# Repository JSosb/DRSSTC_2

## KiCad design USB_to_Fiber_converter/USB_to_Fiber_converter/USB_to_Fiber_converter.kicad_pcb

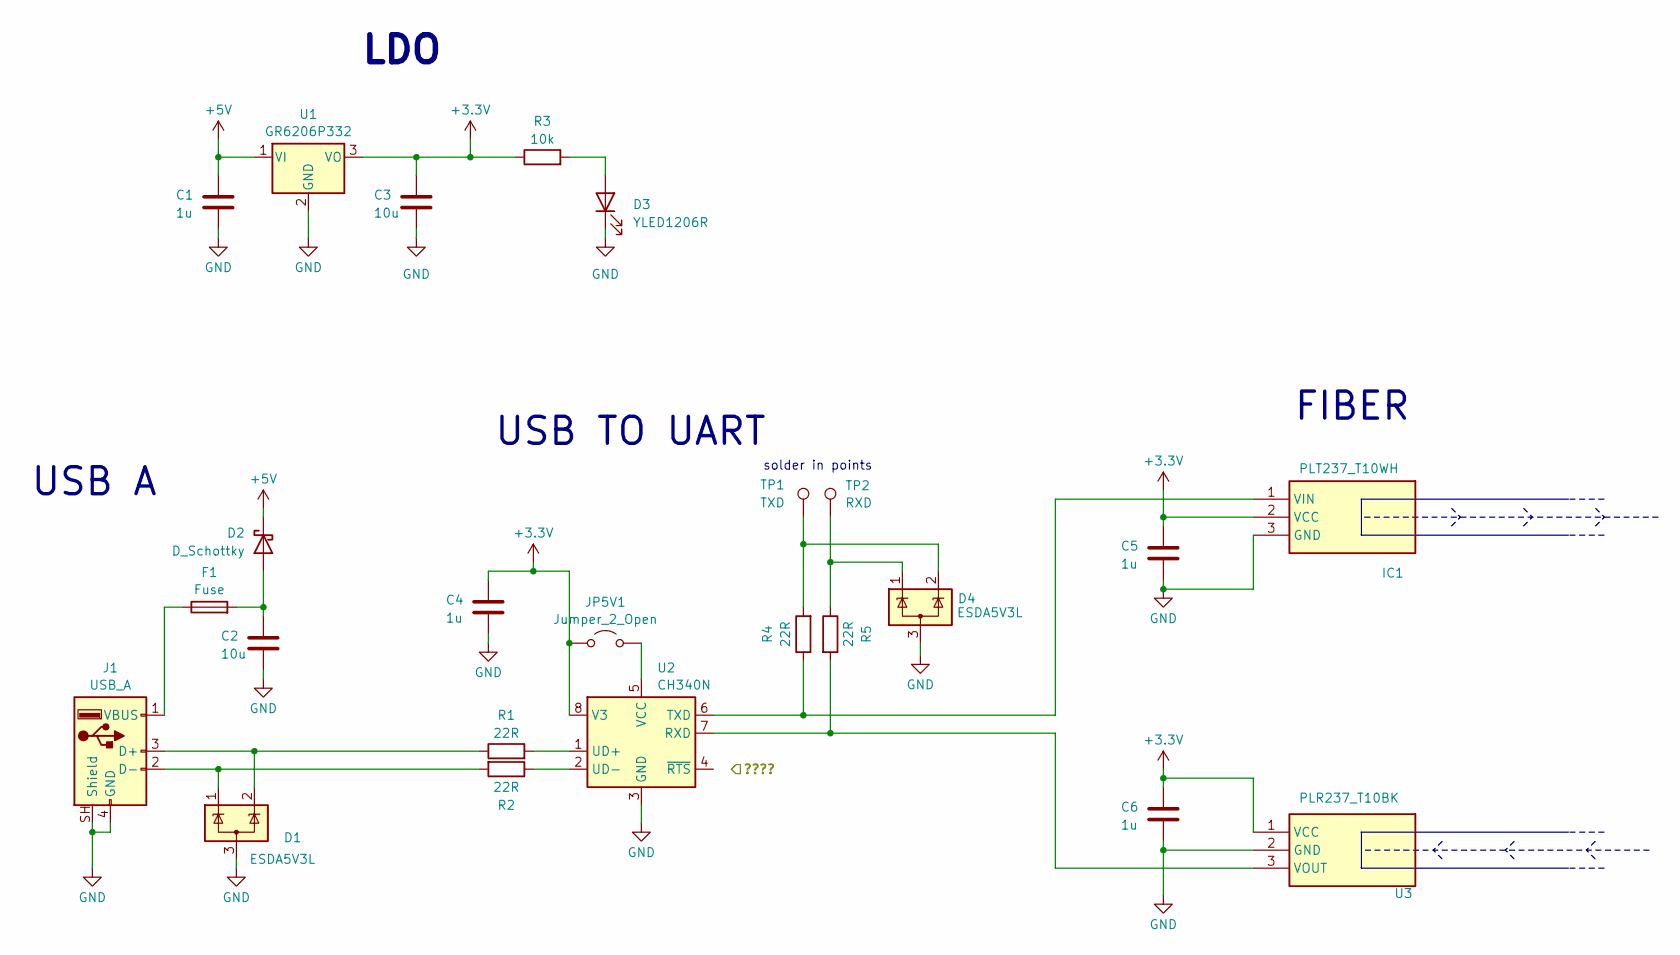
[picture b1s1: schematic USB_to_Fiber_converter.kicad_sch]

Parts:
C1, C4, C5, C6: 1u; C_0603_1608Metric
C2, C3: 10u; C_0805_2012Metric
D1, D4: ESDA5V3L; SOT-23-3
D2: D_Schottky; D_SOD-128
D3: YLED1206R; LED_1206_3216Metric
F1: Fuse; Fuse_2512_6332Metric
IC1: PLT237_T10WH; PLT237T10WH; Mouser Part Number 638-PLT237/T10WH
J1: USB_A; USB_A_Receptacle_GCT_USB1046
JP5V1: Jumper_2_Open; SolderJumper-2_P1.3mm_Open_Pad1.0x1.5mm
R1, R2, R4, R5: 22R; R_0603_1608Metric
R3: 10k; R_0805_2012Metric
TP1: TXD; TestPoint_Pad_2.0x2.0mm
TP2: RXD; TestPoint_Pad_2.0x2.0mm
U1: GR6206P332; SOT-23-3
U2: CH340N; JEITA_SOIC-8_3.9x4.9mm_P1.27mm
U3: PLR237_T10BK; PLR237T10BK; Mouser Part Number 638-PLR237/T10BK

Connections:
+3.3V: C3.1, C4.1, C5.1, C6.1, IC1.2 (VCC), JP5V1.1 (A), R3.1, U1.3 (VO), U2.8 (V3), U3.1 (VCC)
+5V: C1.1, D2.1 (K), U1.1 (VI)
GND: C1.2, C2.2, C3.2, C4.2, C5.2, C6.2, D1.3 (A), D3.1 (K), D4.3 (A), IC1.3 (GND), J1.4 (GND), J1.SH (Shield), U1.2 (GND), U2.3 (GND), U3.2 (GND)
unnamed: C2.1, D2.2 (A), F1.2
unnamed: D3.2 (A), R3.2
unnamed: D4.1 (K), R5.1, TP2.1 (1_1)
unnamed: D4.2 (K), R4.2, TP1.1 (1_1)
unnamed: IC1.1 (VIN), R4.1, U2.6 (TXD)
unnamed: D1.2 (K), J1.3 (D+), R1.1
unnamed: D1.1 (K), J1.2 (D-), R2.2
unnamed: F1.1, J1.1 (VBUS)
unnamed: JP5V1.2 (B), U2.5 (VCC)
unnamed: R5.2, U2.7 (RXD), U3.3 (VOUT)
unnamed: R1.2, U2.1 (UD+)
unnamed: R2.1, U2.2 (UD-)

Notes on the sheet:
FIBER
LDO
USB A
USB TO UART
solder in points

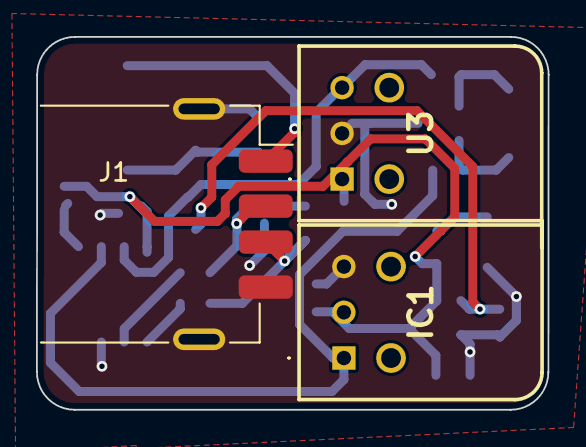
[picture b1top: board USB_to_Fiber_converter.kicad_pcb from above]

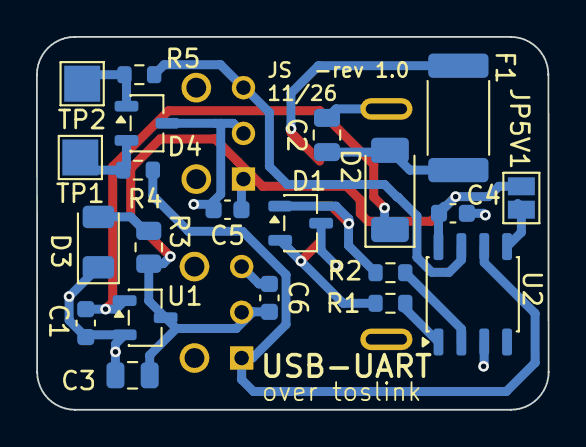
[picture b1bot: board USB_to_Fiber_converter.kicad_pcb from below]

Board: 2 copper layers, 28.4 x 20.7 mm, 24 parts (21 on the bottom side), 15 nets.

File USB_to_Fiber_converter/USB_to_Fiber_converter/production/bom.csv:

Designator,Footprint,Quantity,Value,LCSC Part #
"C1, C4, C5, C6",0603,4,1u,
"C2, C3",0805,2,10u,
"D1, D4",SOT-23-3,2,ESDA5V3L,
D2,D_SOD-128,1,D_Schottky,
D3,1206,1,YLED1206R,
F1,2512,1,Fuse,
IC1,PLT237T10WH,1,PLT237_T10WH,
J1,USB_A_Receptacle_GCT_USB1046,1,USB_A,
JP5V1,SolderJumper-2_P1.3mm_Open_Pad1.0x1.5mm,1,Jumper_2_Open,
"R1, R2, R4, R5",0603,4,22R,
R3,0805,1,10k,
TP1,TestPoint_Pad_2.0x2.0mm,1,TXD,
TP2,TestPoint_Pad_2.0x2.0mm,1,RXD,
U1,SOT-23-3,1,GR6206P332,
U2,JEITA_SOIC-8_3.9x4.9mm_P1.27mm,1,CH340N,
U3,PLR237T10BK,1,PLR237_T10BK,

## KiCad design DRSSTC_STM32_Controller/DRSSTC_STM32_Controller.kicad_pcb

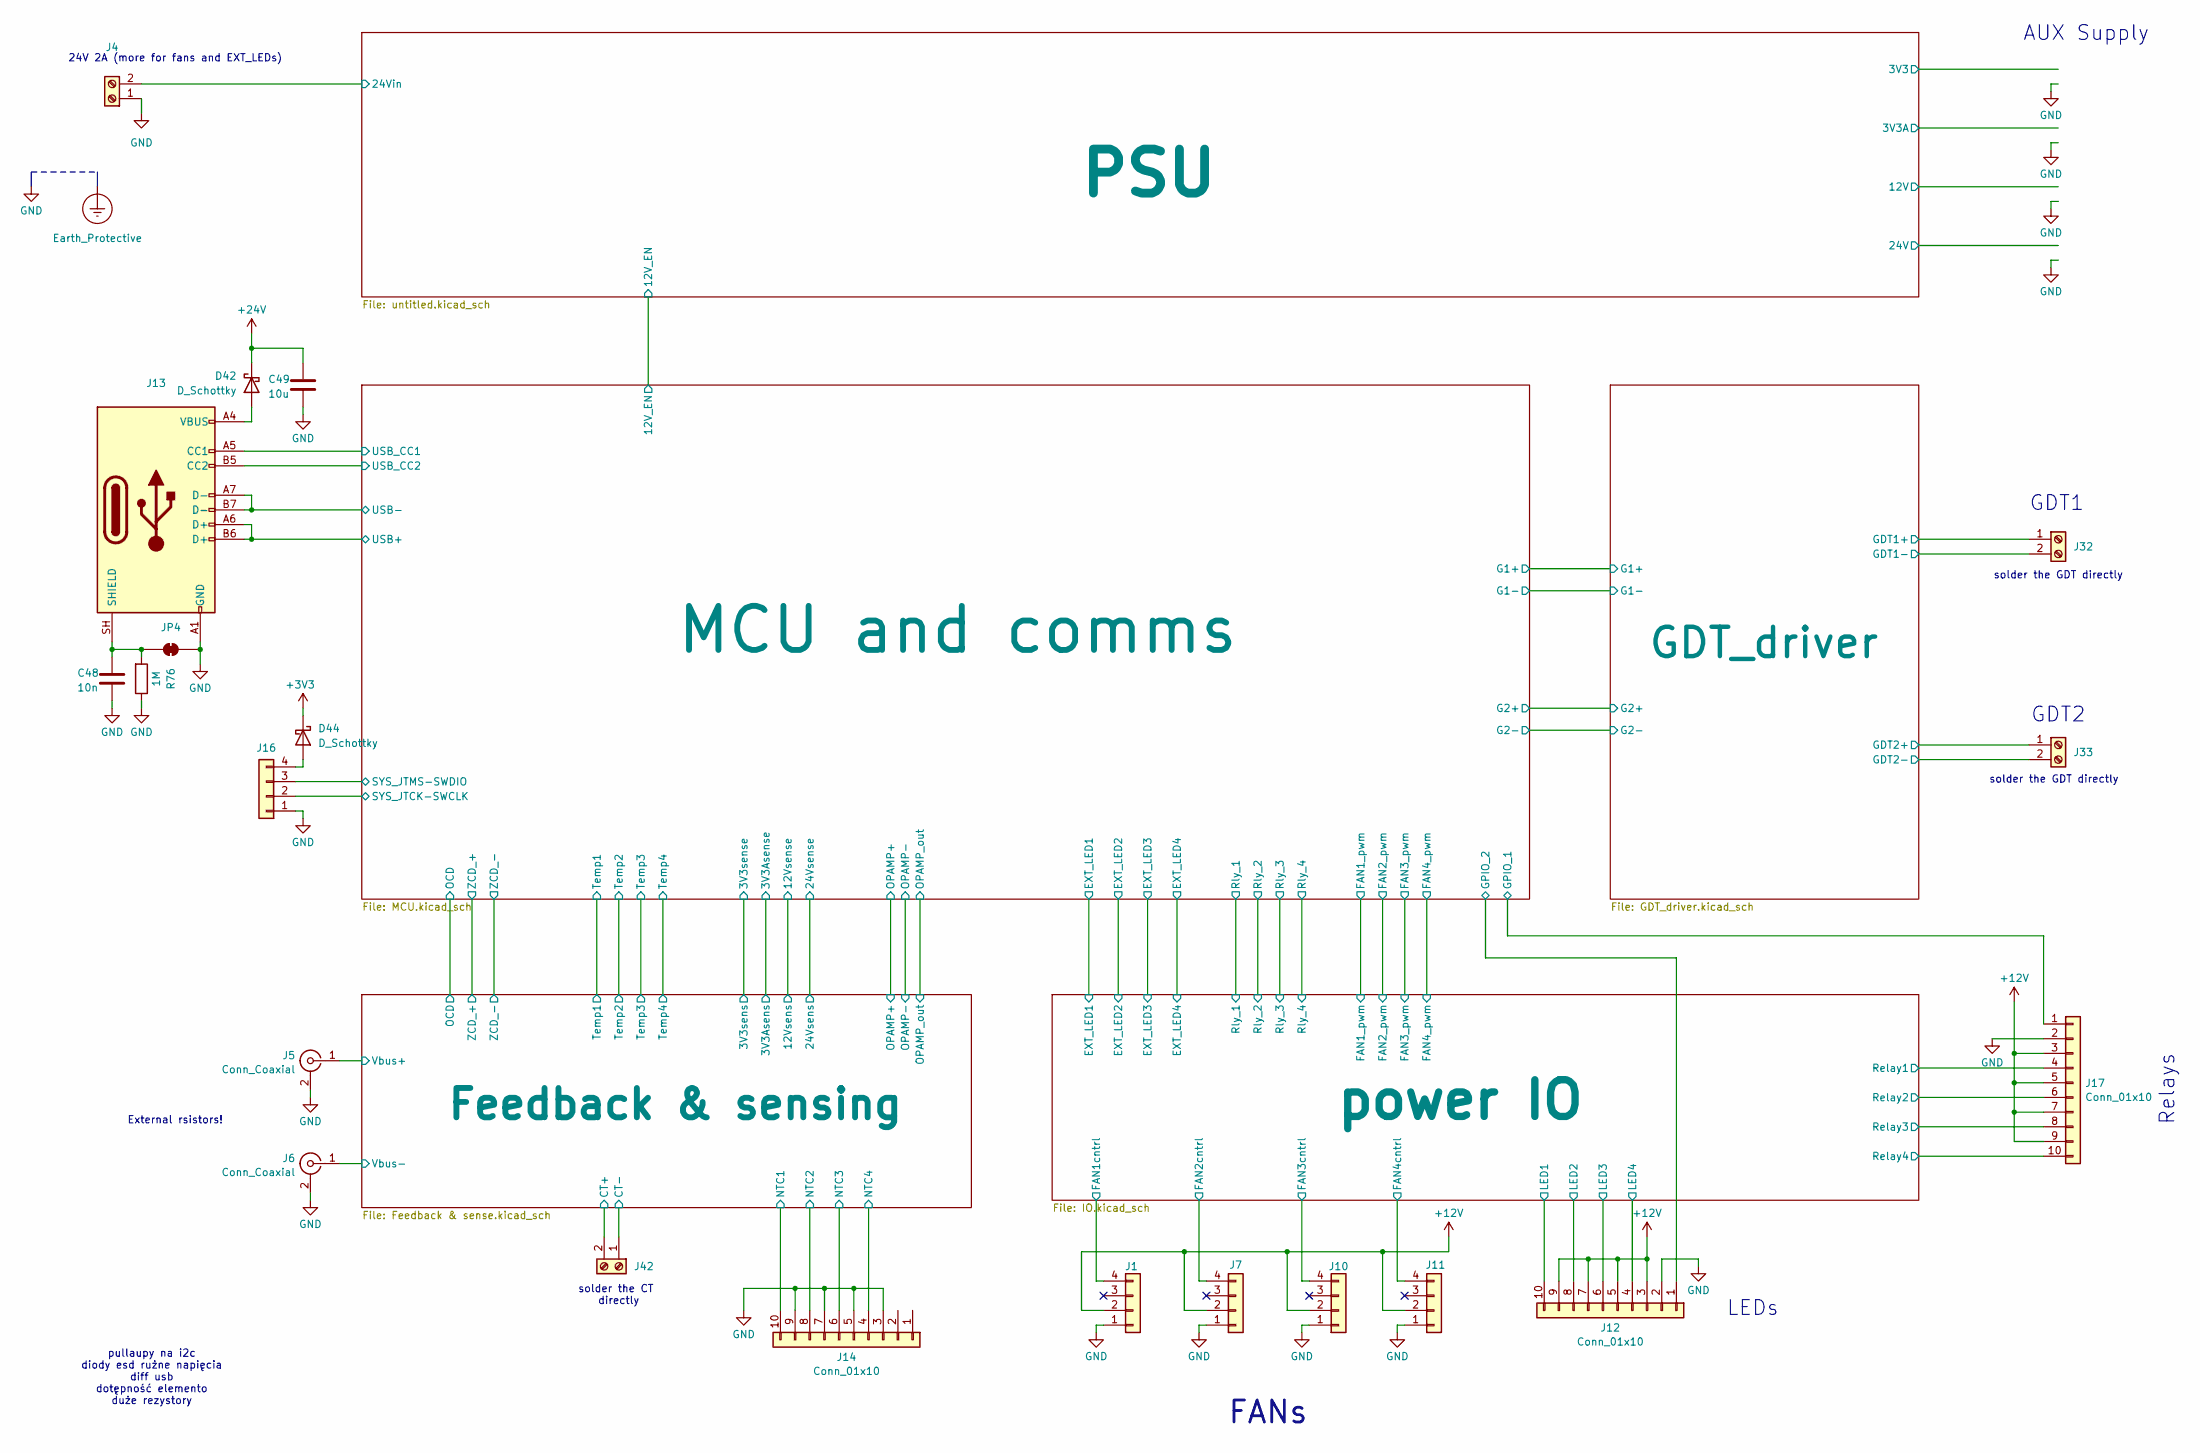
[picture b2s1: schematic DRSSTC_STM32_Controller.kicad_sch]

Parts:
C48: 10n; C_0603_1608Metric
C49: 10u; C_0805_2012Metric
D42, D44: D_Schottky; D_SOD-128
J1, J7, J10, J11: Conn_01x04; 4PIN SMD 2.54
J4: Screw_Terminal_01x02; TerminalBlock_MetzConnect_Type055_RT01502HDWU_1x02_P5.00mm_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
J5, J6: Conn_Coaxial; BNC_TEConnectivity_1478204_Vertical
J12, J14, J17: Conn_01x10; terminal 10pin
J13: USB_C_Receptacle_USB2.0_14P; USB_C_Receptacle_HCTL_HC-TYPE-C-16P-01A
J16: Conn_01x04; PinHeader_1x04_P2.54mm_Vertical
J32, J33, J42: Screw_Terminal_01x02; TerminalBlock_MetzConnect_Type094_RT03502HBLU_1x02_P5.00mm_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
JP4: SolderJumper_2_Bridged; SolderJumper-2_P1.3mm_Bridged2Bar_RoundedPad1.0x1.5mm
R76: 1M; R_0603_1608Metric

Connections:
+3V3: D44.1 (K); also elsewhere on the board
+12V: J1.2, J7.2, J10.2, J11.2, J12.3, J12.5, J12.7, J12.9, J17.3, J17.5, J17.7, J17.9; also elsewhere on the board
+24V: C49.1, D42.1 (K); also elsewhere on the board
/Feedback & sensing/CT+: J42.2; also elsewhere on the board
/Feedback & sensing/CT-: J42.1; also elsewhere on the board
/Feedback & sensing/NTC1: J14.10; also elsewhere on the board
/Feedback & sensing/NTC2: J14.8; also elsewhere on the board
/Feedback & sensing/NTC3: J14.6; also elsewhere on the board
/Feedback & sensing/NTC4: J14.4; also elsewhere on the board
/Feedback & sensing/Vbus+: J5.1 (In); also elsewhere on the board
/Feedback & sensing/Vbus-: J6.1 (In); also elsewhere on the board
/GDT_driver/GDT1+: J32.1; also elsewhere on the board
/GDT_driver/GDT1-: J32.2; also elsewhere on the board
/GDT_driver/GDT2+: J33.1; also elsewhere on the board
/GDT_driver/GDT2-: J33.2; also elsewhere on the board
/MCU and comms/GPIO_1: J17.1; also elsewhere on the board
/MCU and comms/GPIO_2: J12.1; also elsewhere on the board
/MCU and comms/SYS_JTCK-SWCLK: J16.2; also elsewhere on the board
/MCU and comms/SYS_JTMS-SWDIO: J16.3; also elsewhere on the board
/MCU and comms/USB+: J13.A6 (D+), J13.B6 (D+); also elsewhere on the board
/MCU and comms/USB-: J13.A7 (D-), J13.B7 (D-); also elsewhere on the board
/MCU and comms/USB_CC1: J13.A5 (CC1); also elsewhere on the board
/MCU and comms/USB_CC2: J13.B5 (CC2); also elsewhere on the board
/PSU/24Vin: J4.2; also elsewhere on the board
/power IO/FAN1cntrl: J1.4; also elsewhere on the board
/power IO/FAN2cntrl: J7.4; also elsewhere on the board
/power IO/FAN3cntrl: J10.4; also elsewhere on the board
/power IO/FAN4cntrl: J11.4; also elsewhere on the board
/power IO/LED1: J12.10; also elsewhere on the board
/power IO/LED2: J12.8; also elsewhere on the board
/power IO/LED3: J12.6; also elsewhere on the board
/power IO/LED4: J12.4; also elsewhere on the board
/power IO/Relay1: J17.4; also elsewhere on the board
/power IO/Relay2: J17.6; also elsewhere on the board
/power IO/Relay3: J17.8; also elsewhere on the board
/power IO/Relay4: J17.10; also elsewhere on the board
GND: C48.2, C49.2, J1.1, J4.1, J5.2 (Ext), J6.2 (Ext), J7.1, J10.1, J11.1, J12.2, J13.A1 (GND), J13.A12 (GND), J13.B1 (GND), J13.B12 (GND), J14.3, J14.5, J14.7, J14.9, J16.1, J17.2, JP4.1 (A), R76.1; also elsewhere on the board
unnamed: D42.2 (A), J13.A4 (VBUS), J13.A9 (VBUS), J13.B4 (VBUS), J13.B9 (VBUS)
unnamed: D44.2 (A), J16.4
unnamed: C48.1, J13.SH (SHIELD), JP4.2 (B), R76.2

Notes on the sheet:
pullaupy na i2c diody esd rużne napięcia diff usb dotępność elemento duże rezystory
GDT1
AUX Supply
Relays
LEDs
solder the GDT directly
solder the CT directly
External rsistors!
FANs
24V 2A (more for fans and EXT_LEDs)
GDT2

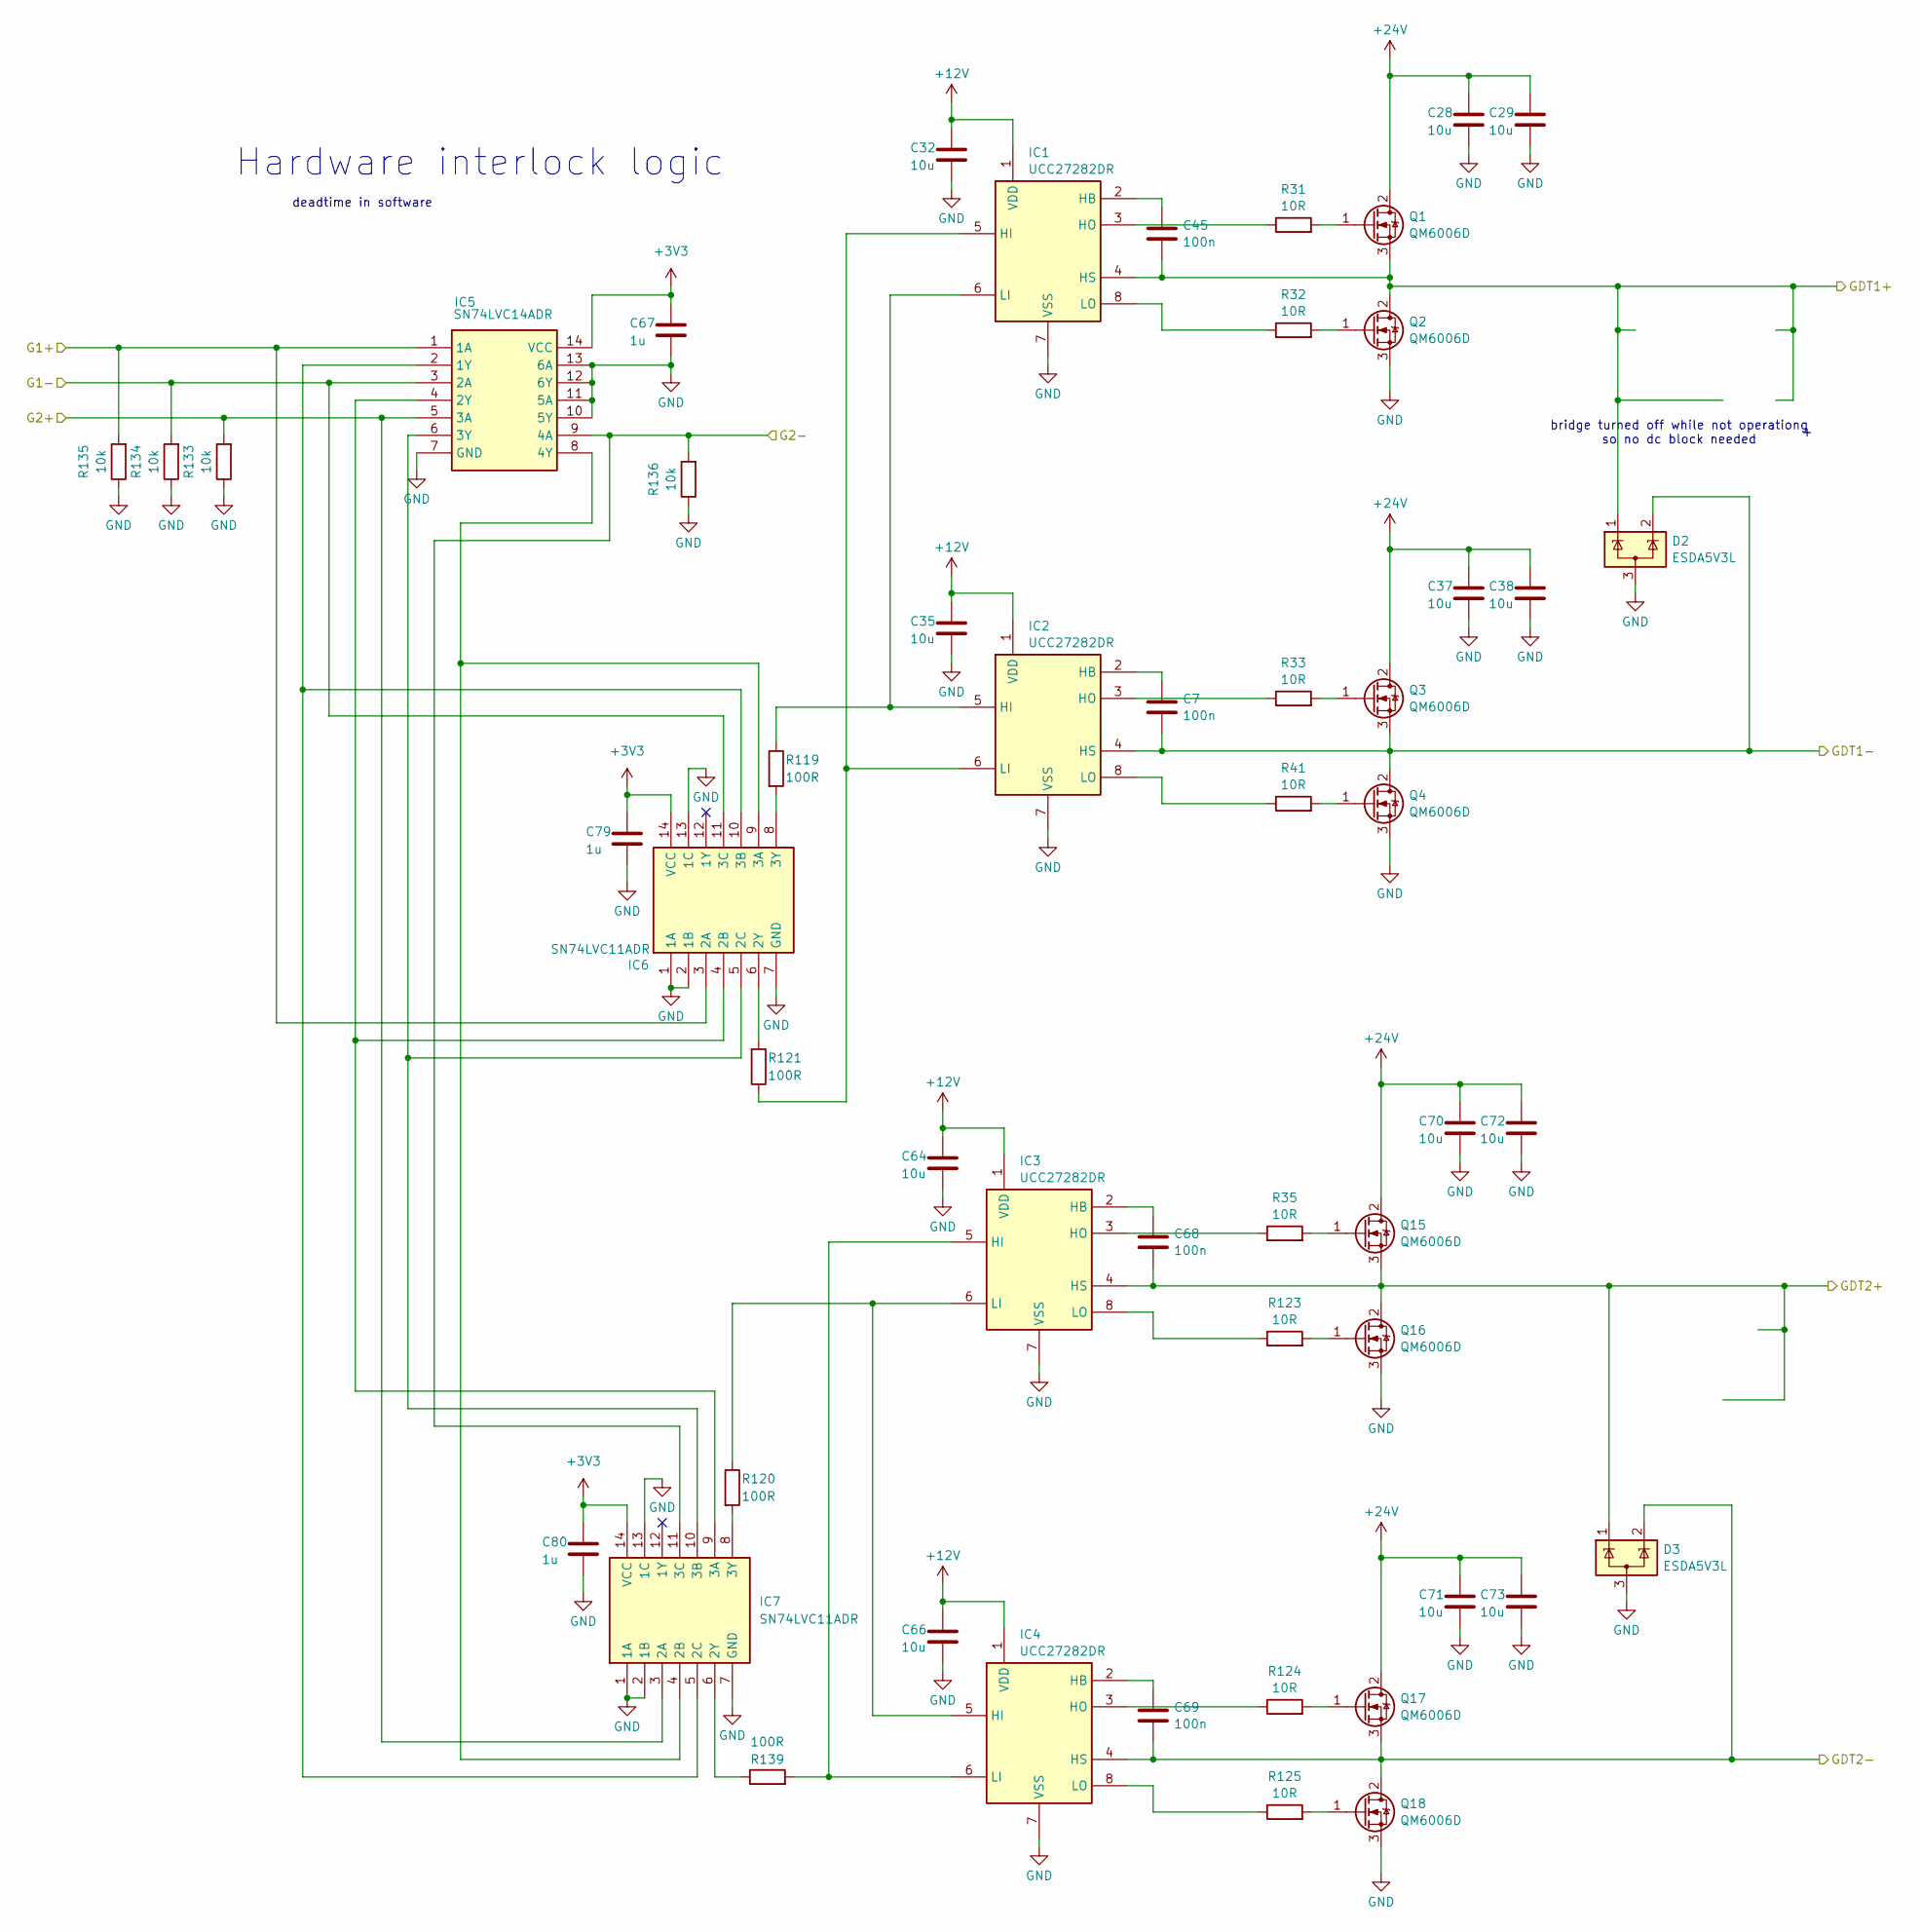
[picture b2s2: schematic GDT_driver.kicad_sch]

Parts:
C7, C45, C68, C69: 100n; C_0603_1608Metric
C28, C29, C32, C35, C37, C38, C64, C66, C70, C71, C72, C73: 10u; C_0805_2012Metric
C67, C79, C80: 1u; C_0603_1608Metric
D2, D3: ESDA5V3L; SOT-23-3
IC1, IC2, IC3, IC4: UCC27282DR; SOIC127P600X175-8N; Mouser Part Number 595-UCC27282DR
IC5: SN74LVC14ADR; SOIC127P600X175-14N; Mouser Part Number 595-SN74LVC14ADR
IC6, IC7: SN74LVC11ADR; SOIC127P600X175-14N; Manufacturer_Part_Number SN74LVC11ADR
Q1, Q2, Q3, Q4, Q15, Q16, Q17, Q18: QM6006D; TO-252-2
R31, R32, R33, R35, R41, R123, R124, R125: 10R; R_0805_2012Metric
R119, R120, R121, R139: 100R; R_0603_1608Metric
R133, R134, R135, R136: 10k; R_0603_1608Metric

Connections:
+3V3: C67.1, C79.1, C80.1, IC5.14 (VCC), IC6.14 (VCC), IC7.14 (VCC); also elsewhere on the board
+12V: C32.1, C35.1, C64.1, C66.1, IC1.1 (VDD), IC2.1 (VDD), IC3.1 (VDD), IC4.1 (VDD); also elsewhere on the board
+24V: C28.1, C29.1, C37.1, C38.1, C70.1, C71.1, C72.1, C73.1, Q1.2 (D), Q3.2 (D), Q15.2 (D), Q17.2 (D); also elsewhere on the board
/GDT_driver/GDT1+: C45.2, D2.1 (K), IC1.4 (HS), Q1.3 (S), Q2.2 (D); also elsewhere on the board
/GDT_driver/GDT1-: C7.2, D2.2 (K), IC2.4 (HS), Q3.3 (S), Q4.2 (D); also elsewhere on the board
/GDT_driver/GDT2+: C68.2, D3.1 (K), IC3.4 (HS), Q15.3 (S), Q16.2 (D); also elsewhere on the board
/GDT_driver/GDT2-: C69.2, D3.2 (K), IC4.4 (HS), Q17.3 (S), Q18.2 (D); also elsewhere on the board
/MCU and comms/G1+: IC5.1 (1A), IC6.3 (2A), R135.2; also elsewhere on the board
/MCU and comms/G1-: IC5.3 (2A), IC6.11 (3C), R134.2; also elsewhere on the board
/MCU and comms/G2+: IC5.5 (3A), IC7.3 (2A), R133.2; also elsewhere on the board
/MCU and comms/G2-: IC5.9 (4A), IC7.11 (3C), R136.2; also elsewhere on the board
GND: C28.2, C29.2, C32.2, C35.2, C37.2, C38.2, C64.2, C66.2, C67.2, C70.2, C71.2, C72.2, C73.2, C79.2, C80.2, D2.3 (A), D3.3 (A), IC1.7 (VSS), IC2.7 (VSS), IC3.7 (VSS), IC4.7 (VSS), IC5.7 (GND), IC5.10 (5Y), IC5.11 (5A), IC5.12 (6Y), IC5.13 (6A), IC6.1 (1A), IC6.2 (1B), IC6.7 (GND), IC6.13 (1C), IC7.1 (1A), IC7.2 (1B), IC7.7 (GND), IC7.13 (1C), Q2.3 (S), Q4.3 (S), Q16.3 (S), Q18.3 (S), R133.1, R134.1, R135.1, R136.1; also elsewhere on the board
unnamed: C45.1, IC1.2 (HB)
unnamed: IC1.5 (HI), IC2.6 (LI), R121.1
unnamed: IC1.3 (HO), R31.1
unnamed: IC1.6 (LI), IC2.5 (HI), R119.1
unnamed: IC1.8 (LO), R32.1
unnamed: C7.1, IC2.2 (HB)
unnamed: IC2.3 (HO), R33.1
unnamed: IC2.8 (LO), R41.1
unnamed: C68.1, IC3.2 (HB)
unnamed: IC3.5 (HI), IC4.6 (LI), R139.2
unnamed: IC3.3 (HO), R35.1
unnamed: IC3.6 (LI), IC4.5 (HI), R120.1
unnamed: IC3.8 (LO), R123.1
unnamed: C69.1, IC4.2 (HB)
unnamed: IC4.3 (HO), R124.1
unnamed: IC4.8 (LO), R125.1
unnamed: IC5.2 (1Y), IC6.10 (3B), IC7.5 (2C)
unnamed: IC5.4 (2Y), IC6.4 (2B), IC7.9 (3A)
unnamed: IC5.6 (3Y), IC6.5 (2C), IC7.10 (3B)
unnamed: IC5.8 (4Y), IC6.9 (3A), IC7.4 (2B)
unnamed: IC6.6 (2Y), R121.2
unnamed: IC6.8 (3Y), R119.2
unnamed: IC7.6 (2Y), R139.1
unnamed: IC7.8 (3Y), R120.2
unnamed: Q1.1 (G), R31.2
unnamed: Q2.1 (G), R32.2
unnamed: Q3.1 (G), R33.2
unnamed: Q4.1 (G), R41.2
unnamed: Q15.1 (G), R35.2
unnamed: Q16.1 (G), R123.2
unnamed: Q17.1 (G), R124.2
unnamed: Q18.1 (G), R125.2

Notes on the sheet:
bridge turned off while not operationg so no dc block needed
Hardware interlock logic
deadtime in software

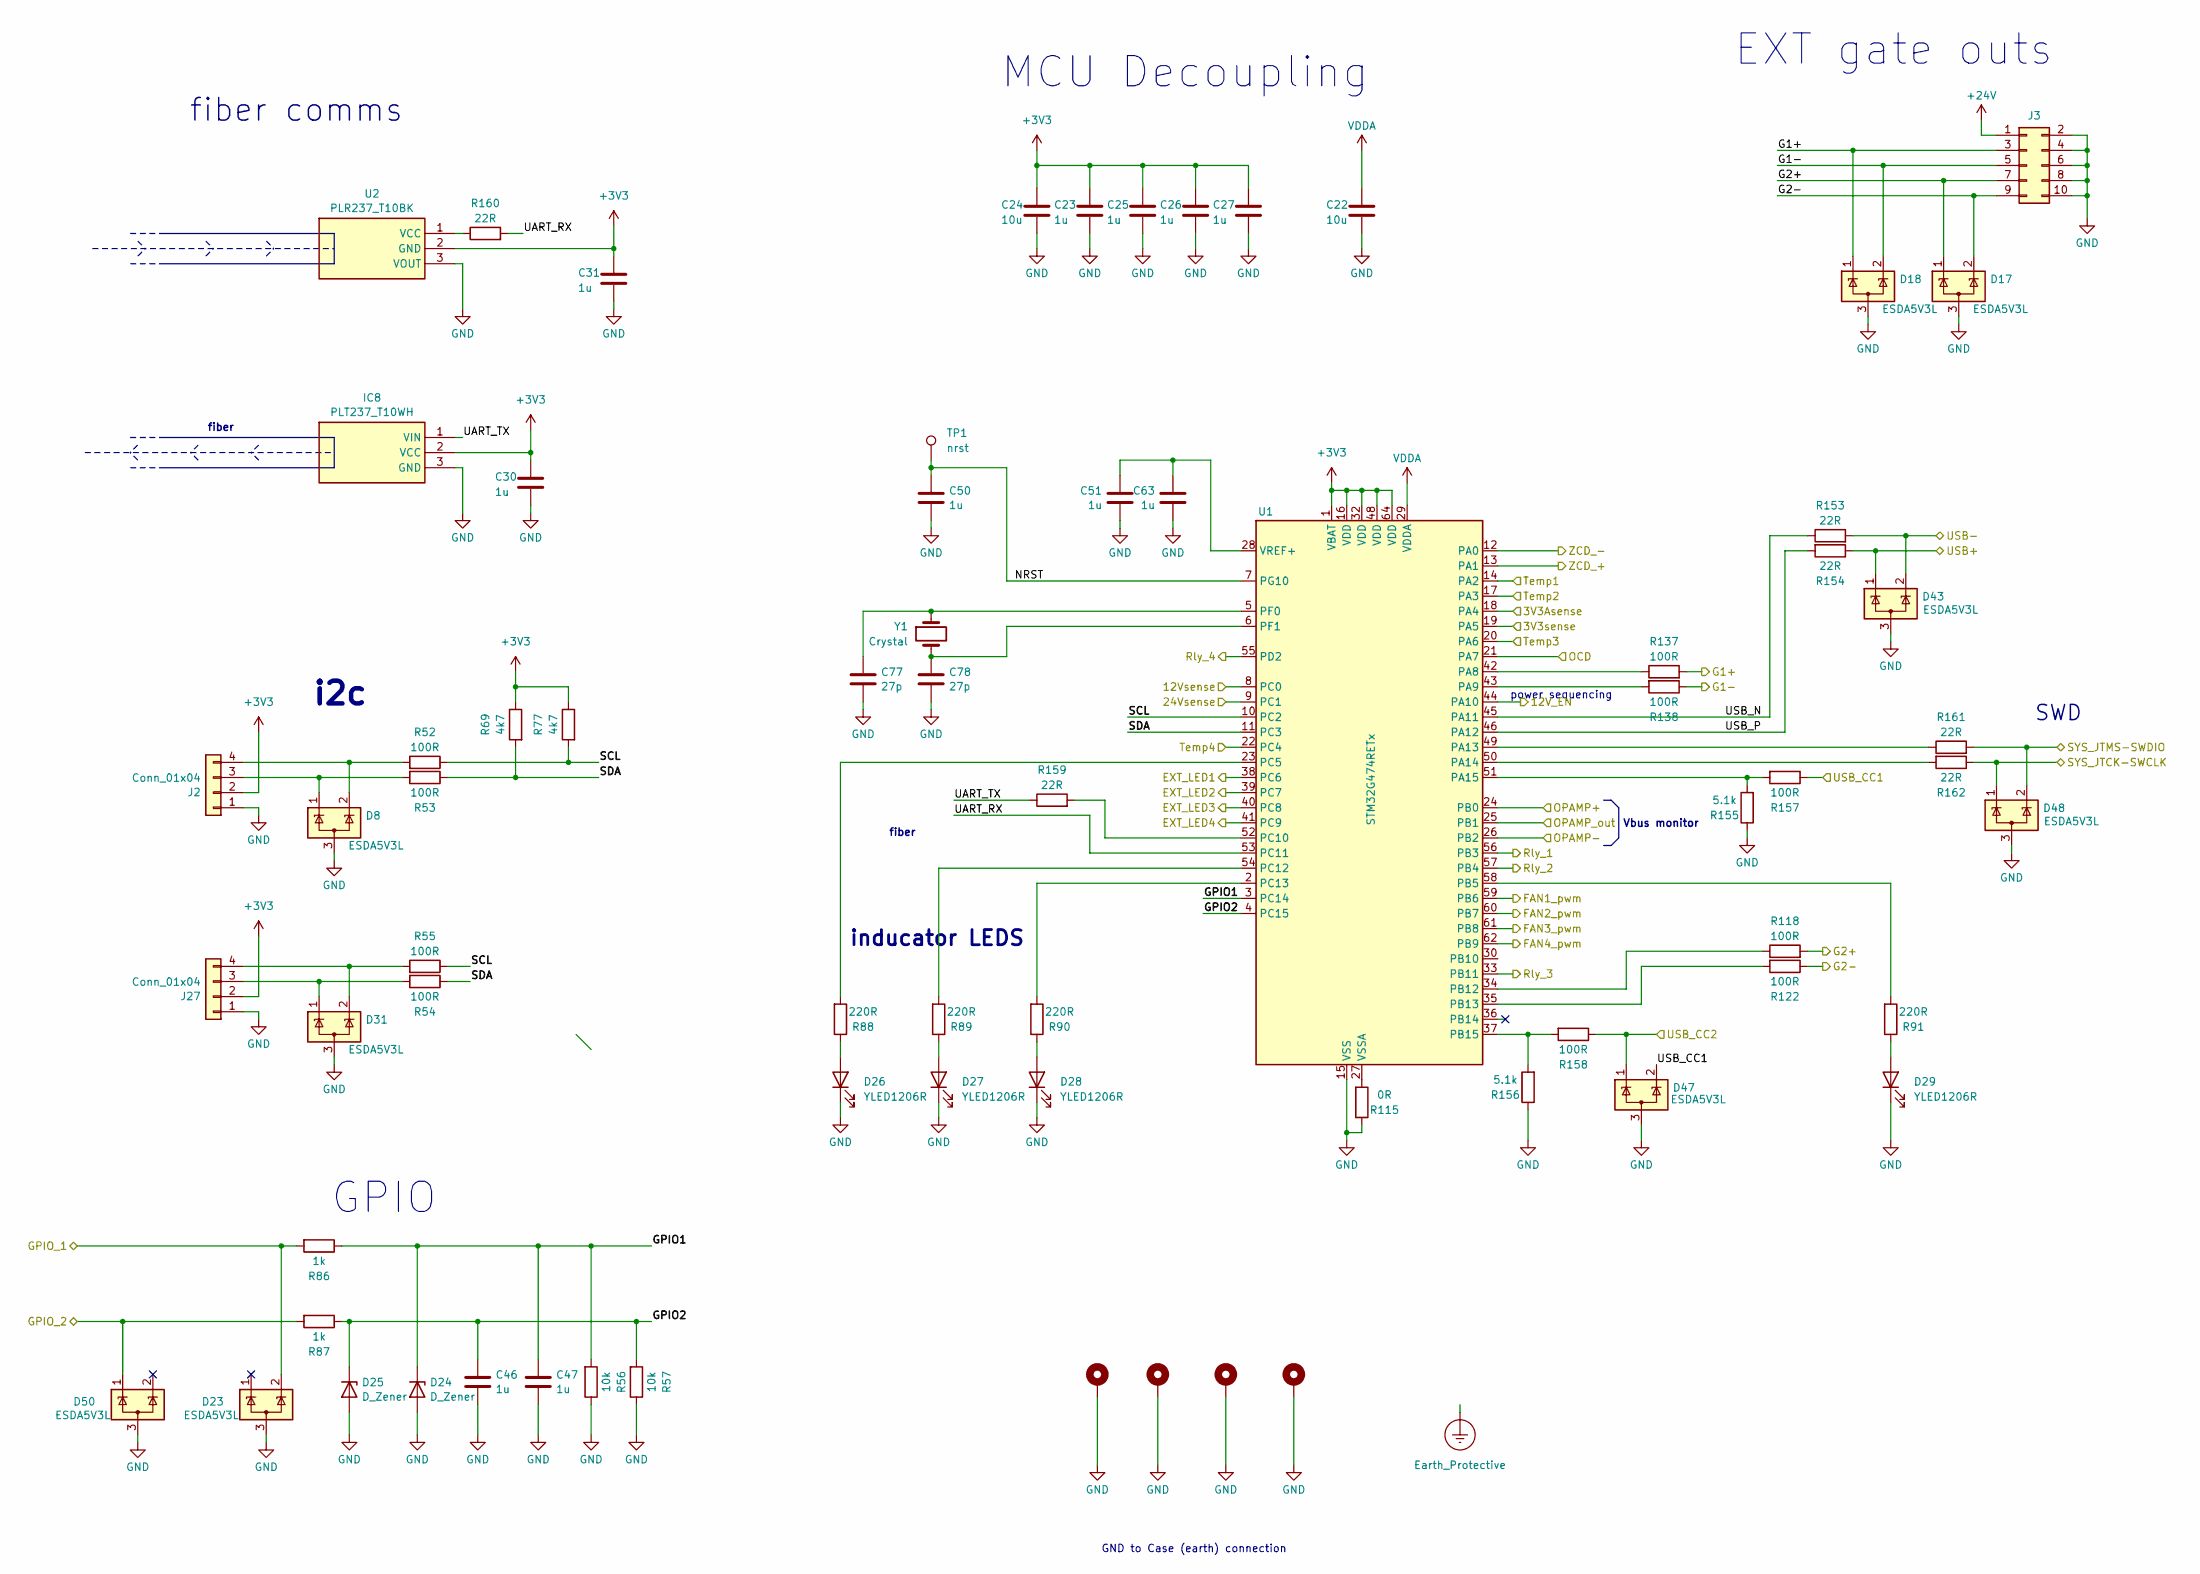
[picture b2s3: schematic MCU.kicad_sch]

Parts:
C22, C24: 10u; C_0805_2012Metric
C23, C25, C26, C27, C30, C31, C46, C47, C50, C51, C63: 1u; C_0603_1608Metric
C77, C78: 27p; C_0603_1608Metric
D8, D17, D18, D23, D31, D43, D47, D48, D50: ESDA5V3L; SOT-23-3
D24, D25: D_Zener; D_SOD-323F
D26, D27, D28, D29: YLED1206R; LED_1206_3216Metric
H4, H5, H6, H7: MountingHole_Pad; MountingHole_3.2mm_M3_Pad_Via
IC8: PLT237_T10WH; PLT237T10WH; Mouser Part Number 638-PLT237/T10WH
J2, J27: Conn_01x04; 4PIN SMD 2.54
J3: Conn_02x05_Odd_Even; IDC-Header_2x05_P2.54mm_Vertical
R52, R53, R54, R55, R118, R122, R137, R138, R157, R158: 100R; R_0603_1608Metric
R56, R57: 10k; R_0603_1608Metric
R69, R77: 4k7; R_0603_1608Metric
R86, R87: 1k; R_0603_1608Metric
R88, R89, R90, R91: 220R; R_0805_2012Metric
R115: 0R; R_0603_1608Metric
R153, R154, R159, R160, R161, R162: 22R; R_0603_1608Metric
R155, R156: 5.1k; R_0603_1608Metric
TP1: nrst; TestPoint_Pad_2.0x2.0mm
U1: STM32G474RETx; LQFP-64_10x10mm_P0.5mm
U2: PLR237_T10BK; PLR237T10BK; Mouser Part Number 638-PLR237/T10BK
Y1: Crystal; Crystal_SMD_3225-4Pin_3.2x2.5mm

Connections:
+3V3: C23.1, C24.1, C25.1, C26.1, C27.1, C30.1, C31.1, IC8.2 (VCC), J2.2, J27.2, R69.1, R77.1, U1.1 (VBAT), U1.16 (VDD), U1.32 (VDD), U1.48 (VDD), U1.64 (VDD), U2.2 (GND); also elsewhere on the board
+24V: J3.1; also elsewhere on the board
/Feedback & sensing/3V3Asens: U1.18 (PA4); also elsewhere on the board
/Feedback & sensing/3V3sens: U1.19 (PA5); also elsewhere on the board
/Feedback & sensing/12Vsens: U1.8 (PC0); also elsewhere on the board
/Feedback & sensing/24Vsens: U1.9 (PC1); also elsewhere on the board
/Feedback & sensing/OCD: U1.21 (PA7); also elsewhere on the board
/Feedback & sensing/OPAMP+: U1.24 (PB0); also elsewhere on the board
/Feedback & sensing/OPAMP-: U1.26 (PB2); also elsewhere on the board
/Feedback & sensing/OPAMP_out: U1.25 (PB1); also elsewhere on the board
/Feedback & sensing/Temp1: U1.14 (PA2); also elsewhere on the board
/Feedback & sensing/Temp2: U1.17 (PA3); also elsewhere on the board
/Feedback & sensing/Temp3: U1.20 (PA6); also elsewhere on the board
/Feedback & sensing/Temp4: U1.22 (PC4); also elsewhere on the board
/Feedback & sensing/ZCD_+: U1.13 (PA1); also elsewhere on the board
/Feedback & sensing/ZCD_-: U1.12 (PA0); also elsewhere on the board
/MCU and comms/12V_EN: U1.44 (PA10); also elsewhere on the board
/MCU and comms/EXT_LED1: U1.38 (PC6); also elsewhere on the board
/MCU and comms/EXT_LED2: U1.39 (PC7); also elsewhere on the board
/MCU and comms/EXT_LED3: U1.40 (PC8); also elsewhere on the board
/MCU and comms/EXT_LED4: U1.41 (PC9); also elsewhere on the board
/MCU and comms/FAN1_pwm: U1.59 (PB6); also elsewhere on the board
/MCU and comms/FAN2_pwm: U1.60 (PB7); also elsewhere on the board
/MCU and comms/FAN3_pwm: U1.61 (PB8); also elsewhere on the board
/MCU and comms/FAN4_pwm: U1.62 (PB9); also elsewhere on the board
/MCU and comms/G1+: D18.1 (K), J3.3, R137.2; also elsewhere on the board
/MCU and comms/G1-: D18.2 (K), J3.5, R138.1; also elsewhere on the board
/MCU and comms/G2+: D17.1 (K), J3.7, R118.2; also elsewhere on the board
/MCU and comms/G2-: D17.2 (K), J3.9, R122.1; also elsewhere on the board
/MCU and comms/GPIO1: C47.1, D24.1 (K), R56.2, R86.1, U1.3 (PC14)
/MCU and comms/GPIO2: C46.1, D25.1 (K), R57.2, R87.1, U1.4 (PC15)
/MCU and comms/GPIO_1: D23.2 (K), R86.2; also elsewhere on the board
/MCU and comms/GPIO_2: D50.1 (K), R87.2; also elsewhere on the board
/MCU and comms/NRST: C50.1, TP1.1 (1_1), U1.7 (PG10)
/MCU and comms/Rly_1: U1.56 (PB3); also elsewhere on the board
/MCU and comms/Rly_2: U1.57 (PB4); also elsewhere on the board
/MCU and comms/Rly_3: U1.33 (PB11); also elsewhere on the board
/MCU and comms/Rly_4: U1.55 (PD2); also elsewhere on the board
/MCU and comms/SCL: R52.1, R55.1, R77.2, U1.10 (PC2)
/MCU and comms/SDA: R53.1, R54.1, R69.2, U1.11 (PC3)
/MCU and comms/SYS_JTCK-SWCLK: D48.1 (K), R162.1; also elsewhere on the board
/MCU and comms/SYS_JTMS-SWDIO: D48.2 (K), R161.2; also elsewhere on the board
/MCU and comms/UART_RX: R160.2, U1.53 (PC11)
/MCU and comms/UART_TX: IC8.1 (VIN), R159.1
/MCU and comms/USB+: D43.1 (K), R154.1; also elsewhere on the board
/MCU and comms/USB-: D43.2 (K), R153.2; also elsewhere on the board
/MCU and comms/USB_CC1: D47.2 (K), R157.1; also elsewhere on the board
/MCU and comms/USB_CC2: D47.1 (K), R158.1; also elsewhere on the board
/MCU and comms/USB_N: R153.1, U1.45 (PA11)
/MCU and comms/USB_P: R154.2, U1.46 (PA12)
GND: C22.2, C23.2, C24.2, C25.2, C26.2, C27.2, C30.2, C31.2, C46.2, C47.2, C50.2, C51.2, C63.2, C77.2, C78.2, D8.3 (A), D17.3 (A), D18.3 (A), D23.3 (A), D24.2 (A), D25.2 (A), D26.1 (K), D27.1 (K), D28.1 (K), D29.1 (K), D31.3 (A), D43.3 (A), D47.3 (A), D48.3 (A), D50.3 (A), H4.1 (1_1), H5.1 (1_1), H6.1 (1_1), H7.1 (1_1), IC8.3 (GND), J2.1, J3.2, J3.4, J3.6, J3.8, J3.10, J27.1, R56.1, R57.1, R115.1, R155.1, R156.1, U1.15 (VSS), U1.31 (VSS), U1.47 (VSS), U1.63 (VSS), U2.3 (VOUT); also elsewhere on the board
unnamed: D26.2 (A), R88.1
unnamed: D27.2 (A), R89.1
unnamed: D28.2 (A), R90.1
unnamed: D29.2 (A), R91.1
unnamed: D8.1 (K), J2.3, R53.2
unnamed: D8.2 (K), J2.4, R52.2
unnamed: D31.1 (K), J27.3, R54.2
unnamed: D31.2 (K), J27.4, R55.2
unnamed: R137.1, U1.42 (PA8)
unnamed: R138.2, U1.43 (PA9)
unnamed: R161.1, U1.49 (PA13)
unnamed: R162.2, U1.50 (PA14)
unnamed: R155.2, R157.2, U1.51 (PA15)
unnamed: R91.2, U1.58 (PB5)
unnamed: R118.1, U1.34 (PB12)
unnamed: R122.2, U1.35 (PB13)
unnamed: R156.2, R158.2, U1.37 (PB15)
unnamed: R88.2, U1.23 (PC5)
unnamed: R159.2, U1.52 (PC10)
unnamed: R89.2, U1.54 (PC12)
unnamed: R90.2, U1.2 (PC13)
unnamed: C77.1, U1.5 (PF0), Y1.1
unnamed: C78.1, U1.6 (PF1), Y1.2
unnamed: C51.1, C63.1, U1.28 (VREF+)
unnamed: R115.2, U1.27 (VSSA)
unnamed: R160.1, U2.1 (VCC)
VDDA: C22.1, U1.29 (VDDA); also elsewhere on the board

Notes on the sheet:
EXT gate outs
power sequencing
SWD
i2c
Vbus monitor
fiber
GPIO
fiber comms
GND to Case (earth) connection
MCU Decoupling
inducator LEDS
